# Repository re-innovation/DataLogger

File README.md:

# DataLogger
A remote datalogging system with many connectivity options.

Based upon the LinkIt One system on a chip board:

https://www.seeedstudio.com/LinkIt-ONE-p-2017.html

https://docs.labs.mediatek.com/resource/linkit-one/en/documentation

## Hardware

PCB has been designed in KiCAD and the files are available in this repository.

PCB has 2 x DC DC converters and a LiIon charger for recharging the battery.

3 x ACS1115 16 bit ADCs are used for monitoring the data.

## Software

The software has been written in C for upload via the Arduino IDE.

A configuration file is used on the SD card which lets the unit know how it needs to work. Set up can easily be done 'in the field'.

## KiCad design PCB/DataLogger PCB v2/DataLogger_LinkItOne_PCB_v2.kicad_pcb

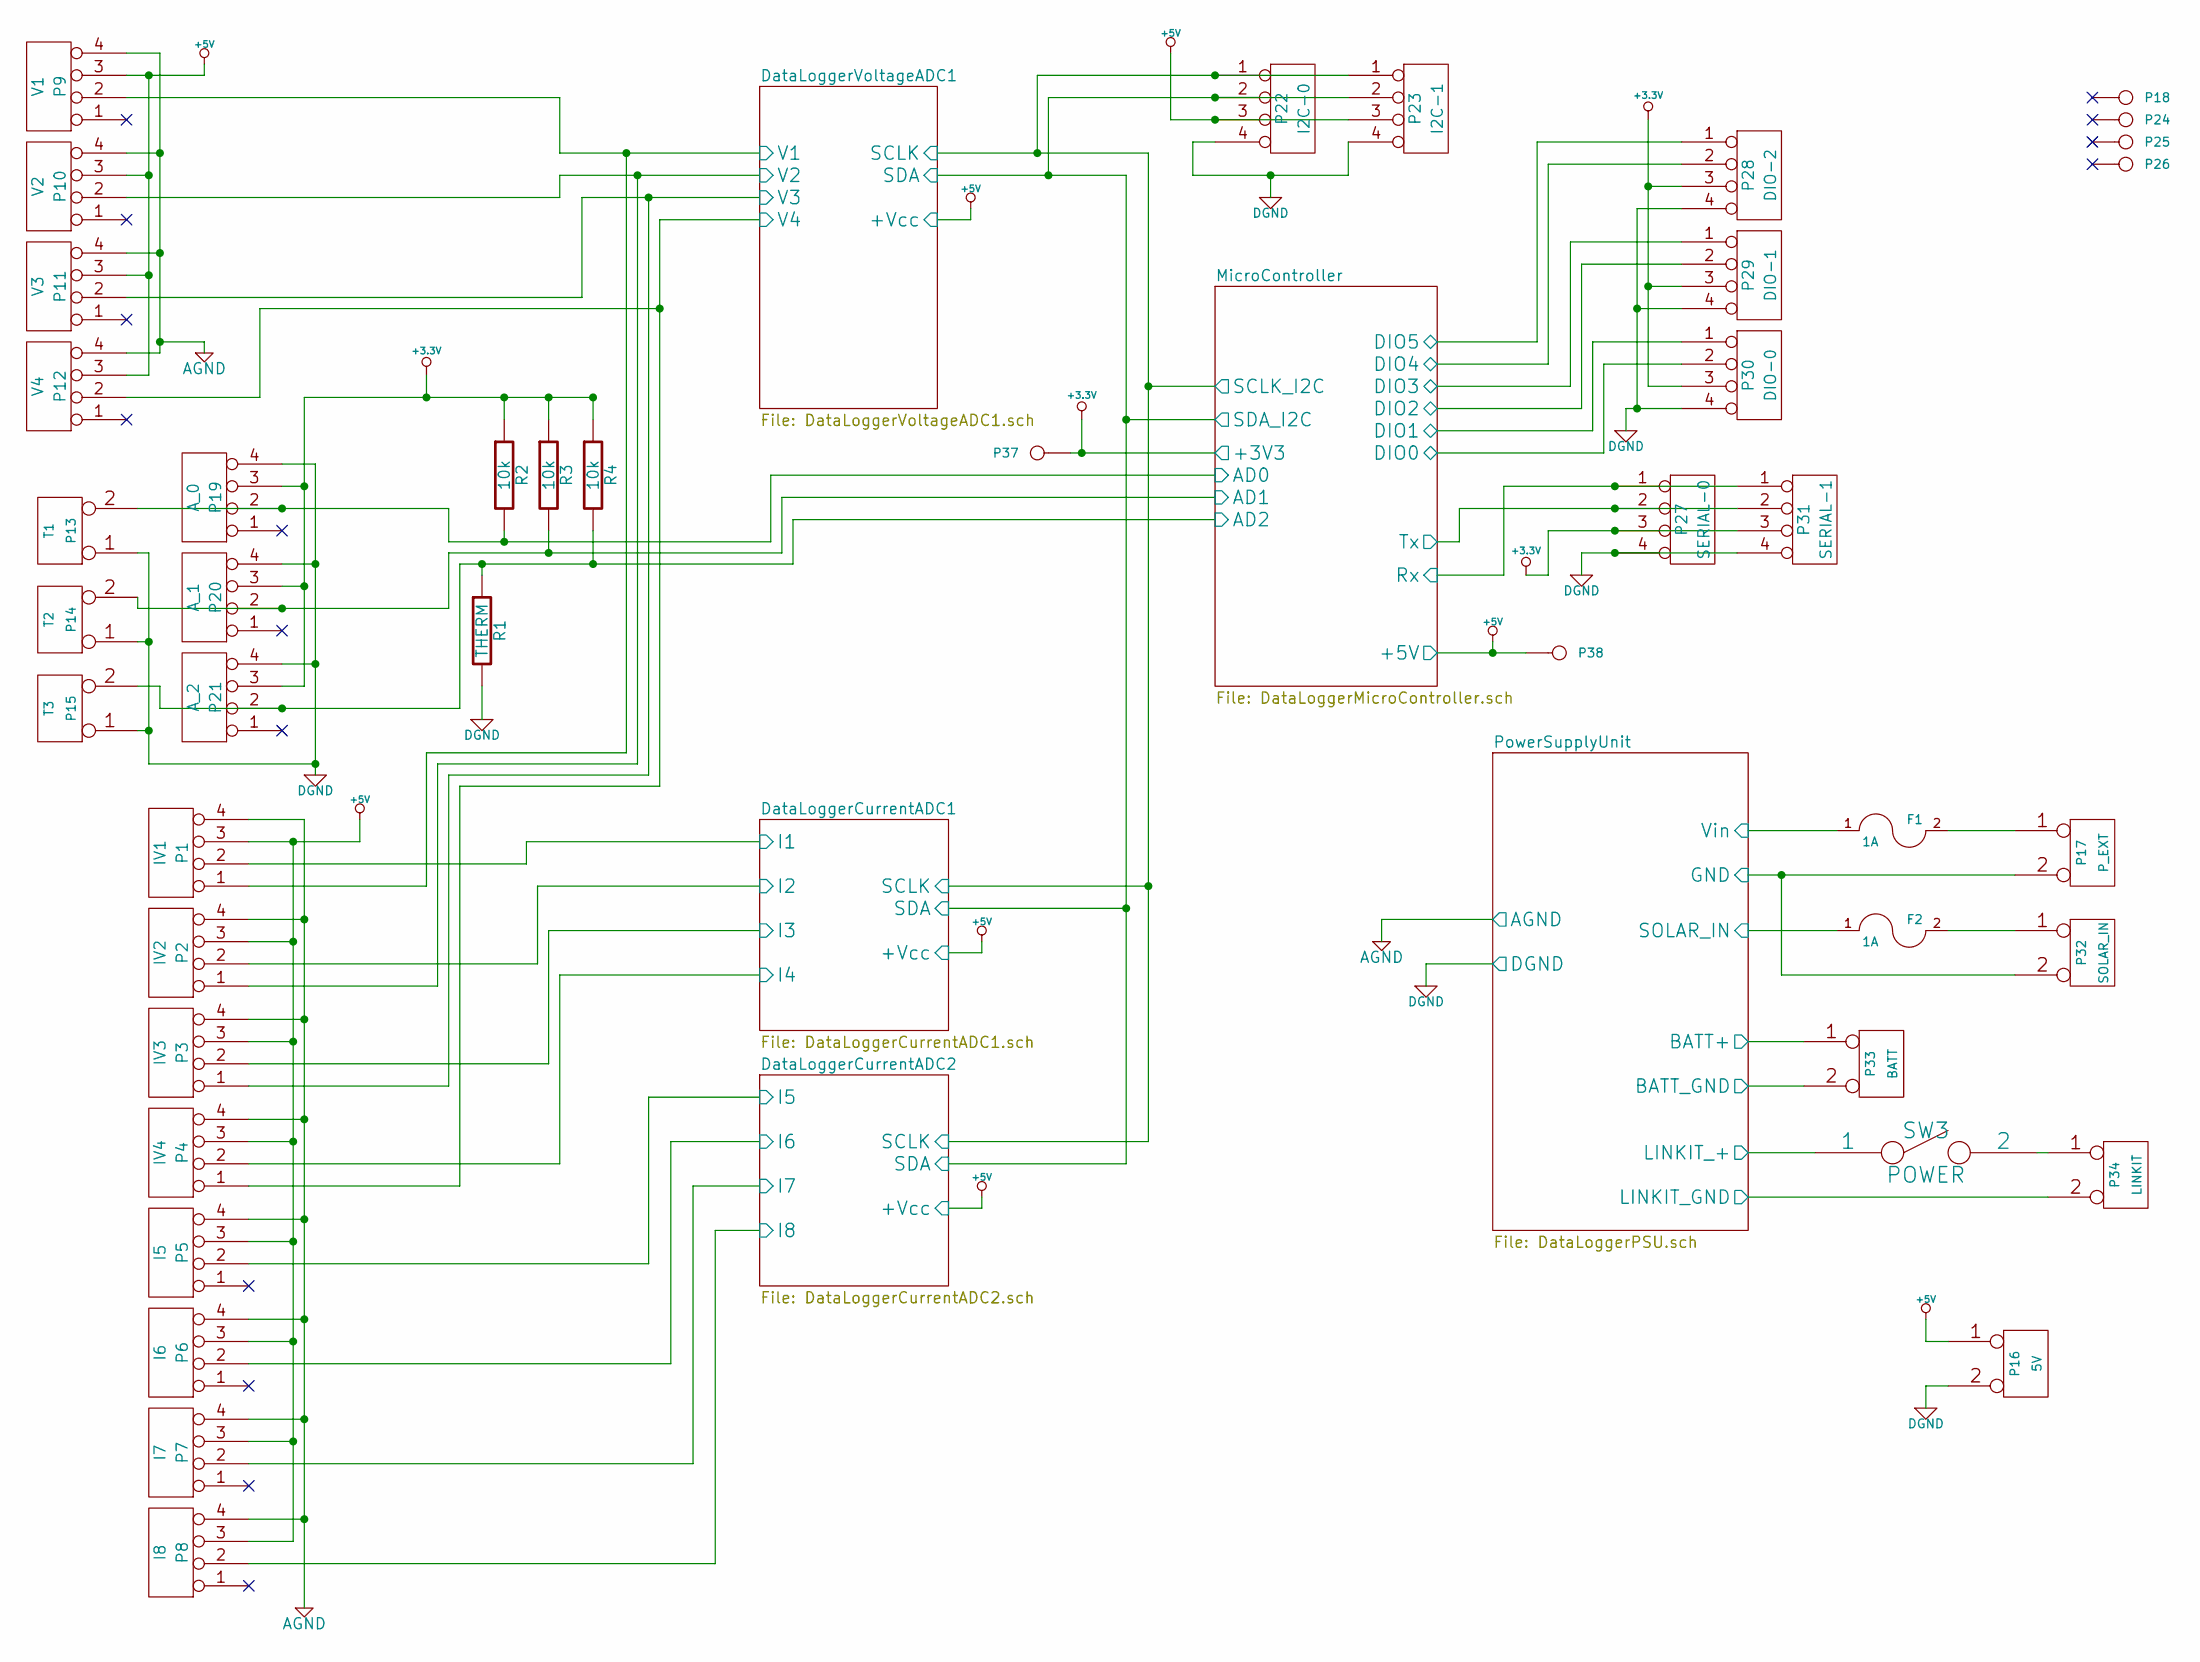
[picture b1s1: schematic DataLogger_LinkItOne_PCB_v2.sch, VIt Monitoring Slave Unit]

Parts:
F1, F2: 1A
P1: IV1
P2: IV2
P3: IV3
P4: IV4
P5: I5
P6: I6
P7: I7
P8: I8
P9: V1
P10: V2
P11: V3
P12: V4
P13: T1
P14: T2
P15: T3
P16: 5V
P17: P_EXT
P18, P24, P25, P26: CONN_1
P19: A_0
P20: A_1
P21: A_2
P22: I2C-0
P23: I2C-1
P27: SERIAL-0
P28: DIO-2
P29: DIO-1
P30: DIO-0
P31: SERIAL-1
P32: SOLAR_IN
P33: BATT
P34: LINKIT
P37: TP33V
P38: TP5V
R1: THERM
R2, R3, R4: 10k
SW3: POWER

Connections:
+3.3V: P19.3, P20.3, P21.3, P27.3, P28.3, P29.3, P30.3, P31.3, P37.1, R2.1, R3.1, R4.1; also elsewhere on the board
+5V: P1.3, P2.3, P3.3, P4.3, P5.3, P6.3, P7.3, P8.3, P9.3, P10.3, P11.3, P12.3, P16.1, P22.3, P23.3, P38.1; also elsewhere on the board
/DataLoggerCurrentADC1/I1: P1.2; also elsewhere on the board
/DataLoggerCurrentADC1/I2: P2.2; also elsewhere on the board
/DataLoggerCurrentADC1/I3: P3.2; also elsewhere on the board
/DataLoggerCurrentADC1/I4: P4.2; also elsewhere on the board
/DataLoggerCurrentADC1/SCLK: P22.1, P23.1; also elsewhere on the board
/DataLoggerCurrentADC1/SDA: P22.2, P23.2; also elsewhere on the board
/DataLoggerCurrentADC2/I5: P5.2; also elsewhere on the board
/DataLoggerCurrentADC2/I6: P6.2; also elsewhere on the board
/DataLoggerCurrentADC2/I7: P7.2; also elsewhere on the board
/DataLoggerCurrentADC2/I8: P8.2; also elsewhere on the board
/DataLoggerVoltageADC1/V1: P1.1, P9.2; also elsewhere on the board
/DataLoggerVoltageADC1/V2: P2.1, P10.2; also elsewhere on the board
/DataLoggerVoltageADC1/V3: P3.1, P11.2; also elsewhere on the board
/DataLoggerVoltageADC1/V4: P4.1, P12.2; also elsewhere on the board
/MicroController/AD0: P13.2 (PM), P19.2, R2.2; also elsewhere on the board
/MicroController/AD1: P14.2 (PM), P20.2, R3.2; also elsewhere on the board
/MicroController/AD2: P15.2 (PM), P21.2, R1.1, R4.2; also elsewhere on the board
/MicroController/DIO0: P30.2; also elsewhere on the board
/MicroController/DIO1: P30.1; also elsewhere on the board
/MicroController/DIO2: P29.2; also elsewhere on the board
/MicroController/DIO3: P29.1; also elsewhere on the board
/MicroController/DIO4: P28.2; also elsewhere on the board
/MicroController/DIO5: P28.1; also elsewhere on the board
/MicroController/Rx: P27.1, P31.1; also elsewhere on the board
/MicroController/Tx: P27.2, P31.2; also elsewhere on the board
/PowerSupplyUnit/BATT+: P33.1, SW3.1; also elsewhere on the board
/PowerSupplyUnit/SOLAR_IN: F2.1; also elsewhere on the board
/PowerSupplyUnit/Vin: F1.1; also elsewhere on the board
AGND: P1.4, P2.4, P3.4, P4.4, P5.4, P6.4, P7.4, P8.4, P9.4, P10.4, P11.4, P12.4; also elsewhere on the board
DGND: P13.1, P14.1, P15.1, P16.2 (PM), P17.2 (PM), P19.4, P20.4, P21.4, P22.4, P23.4, P27.4, P28.4, P29.4, P30.4, P31.4, P32.2 (PM), P33.2 (PM), P34.2 (PM), R1.2; also elsewhere on the board
unnamed: F1.2, P17.1
unnamed: P34.1, SW3.2
unnamed: F2.2, P32.1

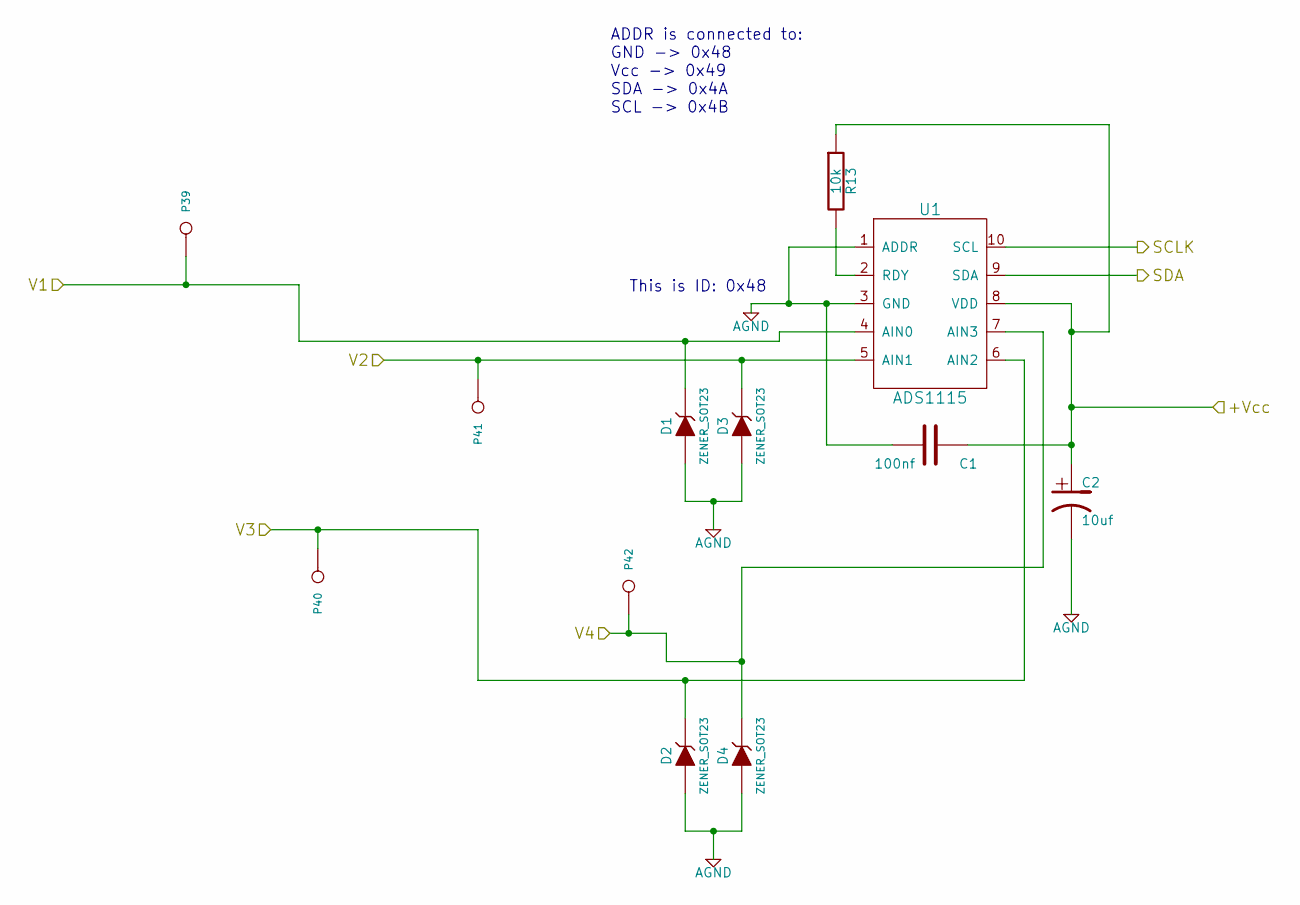
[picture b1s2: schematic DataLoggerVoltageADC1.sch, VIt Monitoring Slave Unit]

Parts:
C1: 100nf
C2: 10uf
D1, D2, D3, D4: ZENER_SOT23
P39: TPV1
P40: TPV3
P41: TPV2
P42: TPV4
R13: 10k
U1: ADS1115

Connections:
+5V: C1.1, C2.1, R13.1, U1.8 (VDD); also elsewhere on the board
/DataLoggerCurrentADC1/SCLK: U1.10 (SCL); also elsewhere on the board
/DataLoggerCurrentADC1/SDA: U1.9 (SDA); also elsewhere on the board
/DataLoggerVoltageADC1/V1: D1.3 (K), P39.1, U1.4 (AIN0); also elsewhere on the board
/DataLoggerVoltageADC1/V2: D3.3 (K), P41.1, U1.5 (AIN1); also elsewhere on the board
/DataLoggerVoltageADC1/V3: D2.3 (K), P40.1, U1.6 (AIN2); also elsewhere on the board
/DataLoggerVoltageADC1/V4: D4.3 (K), P42.1, U1.7 (AIN3); also elsewhere on the board
AGND: C1.2, C2.2, D1.1 (A), D2.1 (A), D3.1 (A), D4.1 (A), U1.1 (ADDR), U1.3 (GND); also elsewhere on the board
unnamed: R13.2, U1.2 (RDY)

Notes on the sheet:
ADDR is connected to: GND -> 0x48 Vcc -> 0x49 SDA -> 0x4A SCL -> 0x4B
This is ID: 0x48

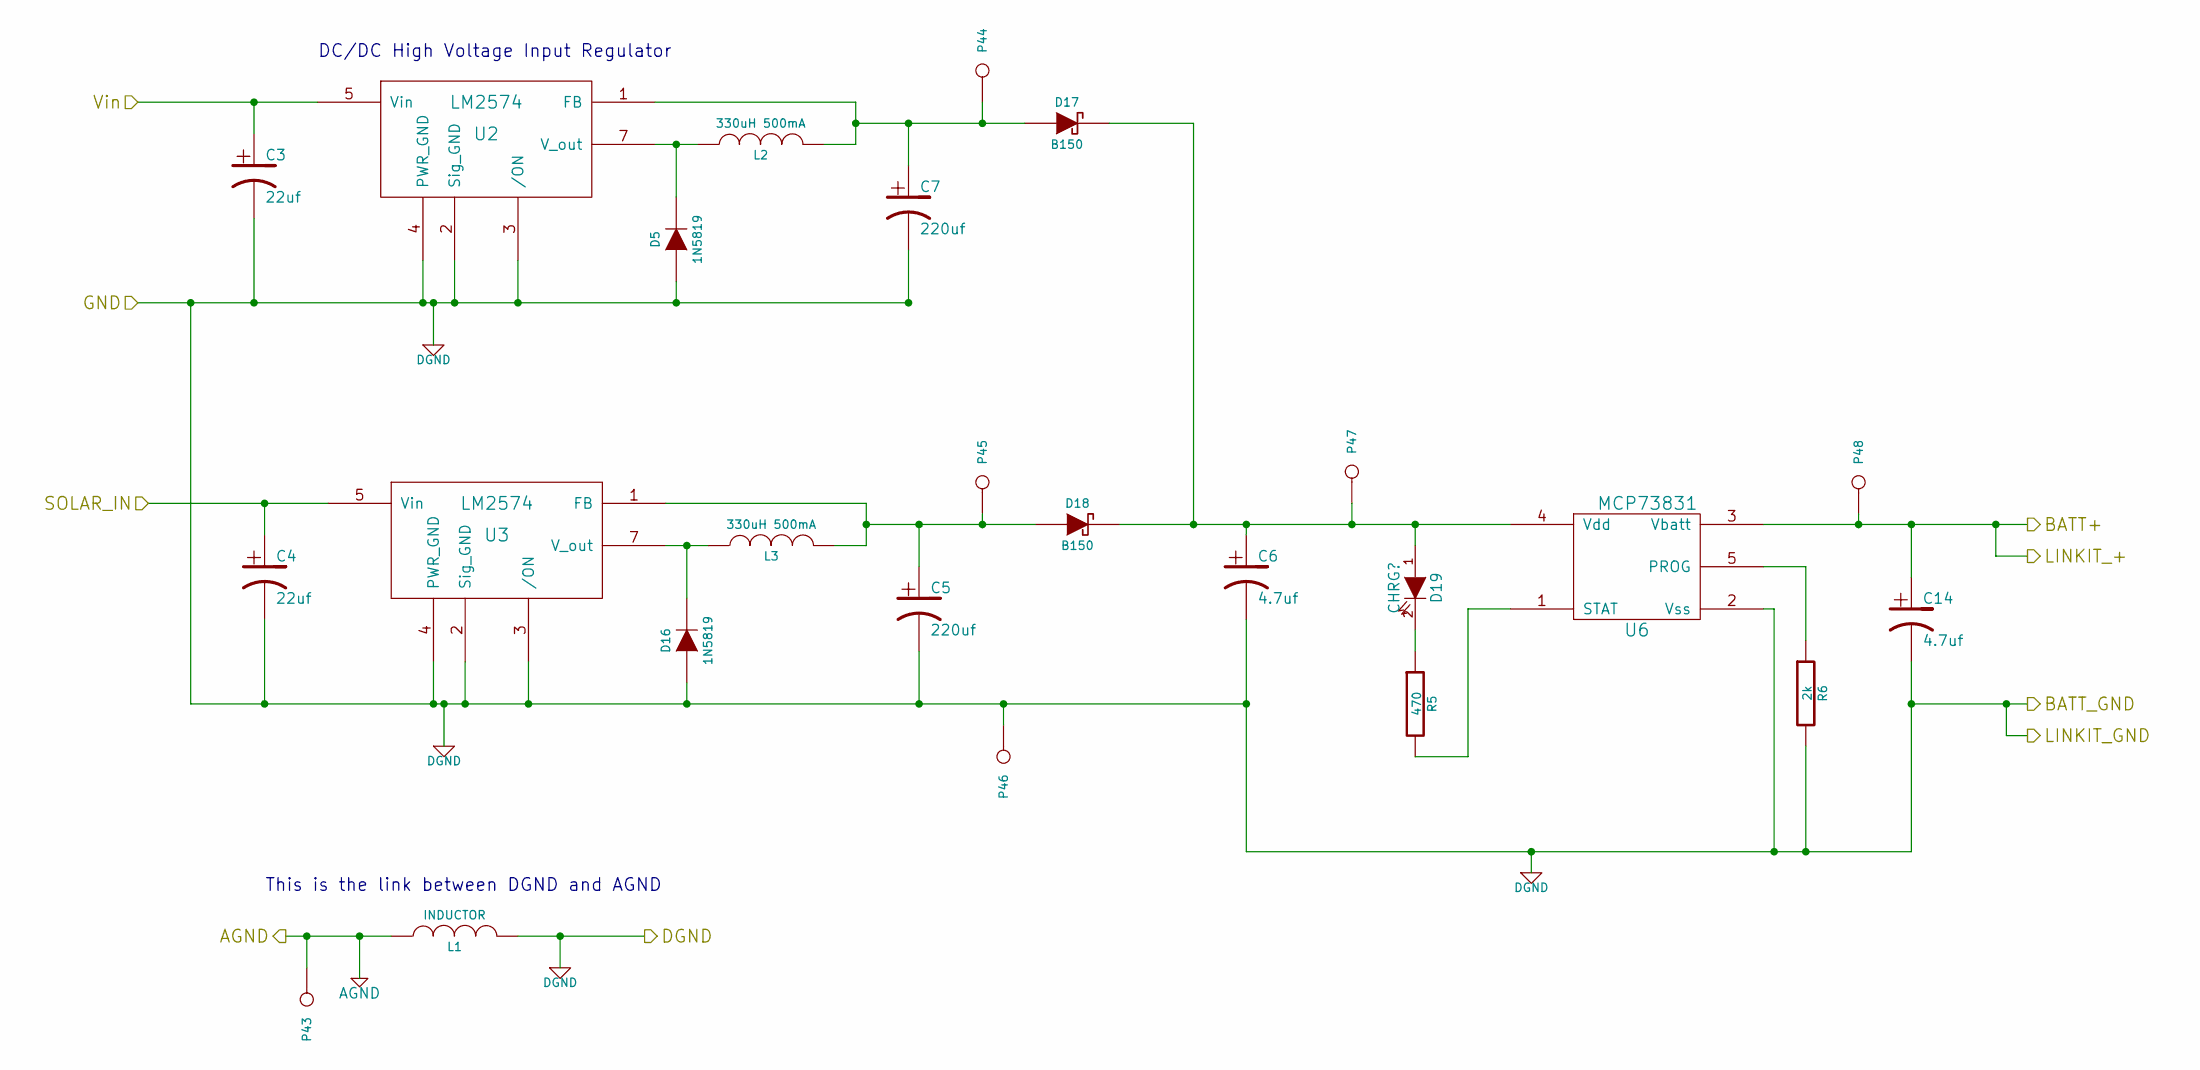
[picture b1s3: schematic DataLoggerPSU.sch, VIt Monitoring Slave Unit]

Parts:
C3, C4: 22uf
C5, C7: 220uf
C6, C14: 4.7uf
D5, D16: 1N5819
D17, D18: B150
D19: CHRG?
L1: INDUCTOR
L2, L3: 330uH 500mA
P43: TPAG
P44: TPP1
P45: TPP2
P46: TPDG
P47: TPP3
P48: TPBATT
R5: 470
R6: 2k
U2, U3: LM2574
U6: MCP73831

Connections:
/PowerSupplyUnit/BATT+: C14.1, P48.1, U6.3 (Vbatt); also elsewhere on the board
/PowerSupplyUnit/SOLAR_IN: C4.1, U3.5 (Vin); also elsewhere on the board
/PowerSupplyUnit/Vin: C3.1, U2.5 (Vin); also elsewhere on the board
AGND: L1.1, P43.1; also elsewhere on the board
DGND: C3.2, C4.2, C5.2, C6.2, C7.2, C14.2, D5.1 (A), D16.1 (A), L1.2, P46.1, R6.2, U2.2 (Sig_GND), U2.3 (/ON), U2.4 (PWR_GND), U3.2 (Sig_GND), U3.3 (/ON), U3.4 (PWR_GND), U6.2 (Vss); also elsewhere on the board
unnamed: R5.2, U6.1 (STAT)
unnamed: D19.2 (K), R5.1
unnamed: R6.1, U6.5 (PROG)
unnamed: D5.2 (K), L2.1, U2.7 (V_out)
unnamed: C7.1, D17.2 (A), L2.2, P44.1, U2.1 (FB)
unnamed: C6.1, D17.1 (K), D18.1 (K), D19.1 (A), P47.1, U6.4 (Vdd)
unnamed: C5.1, D18.2 (A), L3.2, P45.1, U3.1 (FB)
unnamed: D16.2 (K), L3.1, U3.7 (V_out)

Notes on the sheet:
DC/DC High Voltage Input Regulator
This is the link between DGND and AGND

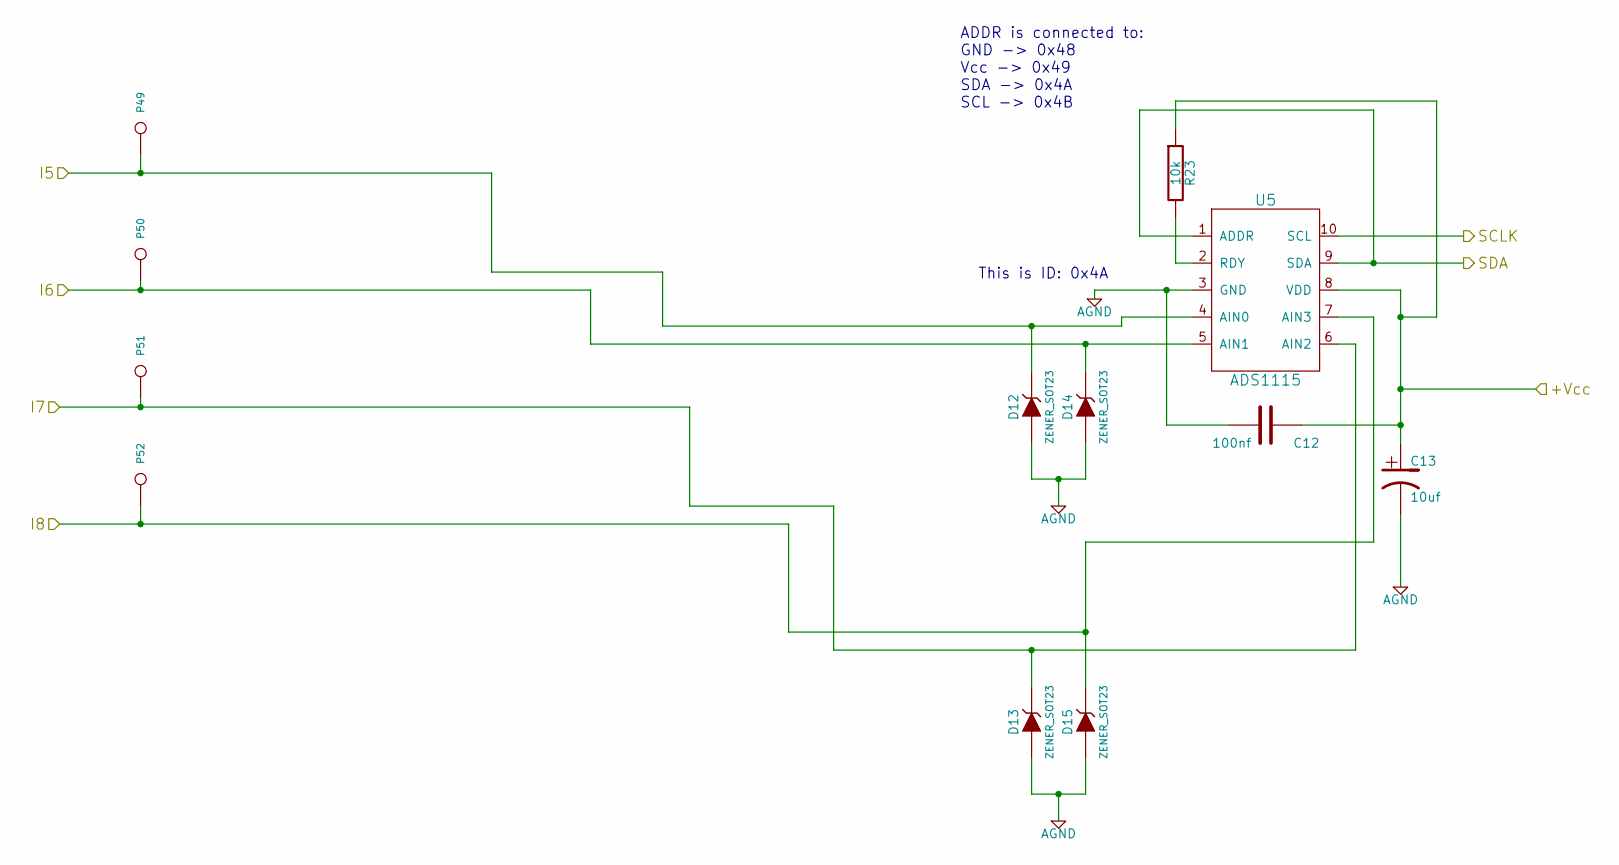
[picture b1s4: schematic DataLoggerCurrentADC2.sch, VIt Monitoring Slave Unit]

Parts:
C12: 100nf
C13: 10uf
D12, D13, D14, D15: ZENER_SOT23
P49: TPI5
P50: TPI6
P51: TPI7
P52: TPI8
R23: 10k
U5: ADS1115

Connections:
+5V: C12.1, C13.1, R23.1, U5.8 (VDD); also elsewhere on the board
/DataLoggerCurrentADC1/SCLK: U5.10 (SCL); also elsewhere on the board
/DataLoggerCurrentADC1/SDA: U5.1 (ADDR), U5.9 (SDA); also elsewhere on the board
/DataLoggerCurrentADC2/I5: D12.3 (K), P49.1, U5.4 (AIN0); also elsewhere on the board
/DataLoggerCurrentADC2/I6: D14.3 (K), P50.1, U5.5 (AIN1); also elsewhere on the board
/DataLoggerCurrentADC2/I7: D13.3 (K), P51.1, U5.6 (AIN2); also elsewhere on the board
/DataLoggerCurrentADC2/I8: D15.3 (K), P52.1, U5.7 (AIN3); also elsewhere on the board
AGND: C12.2, C13.2, D12.1 (A), D13.1 (A), D14.1 (A), D15.1 (A), U5.3 (GND); also elsewhere on the board
unnamed: R23.2, U5.2 (RDY)

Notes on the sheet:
ADDR is connected to: GND -> 0x48 Vcc -> 0x49 SDA -> 0x4A SCL -> 0x4B
This is ID: 0x4A

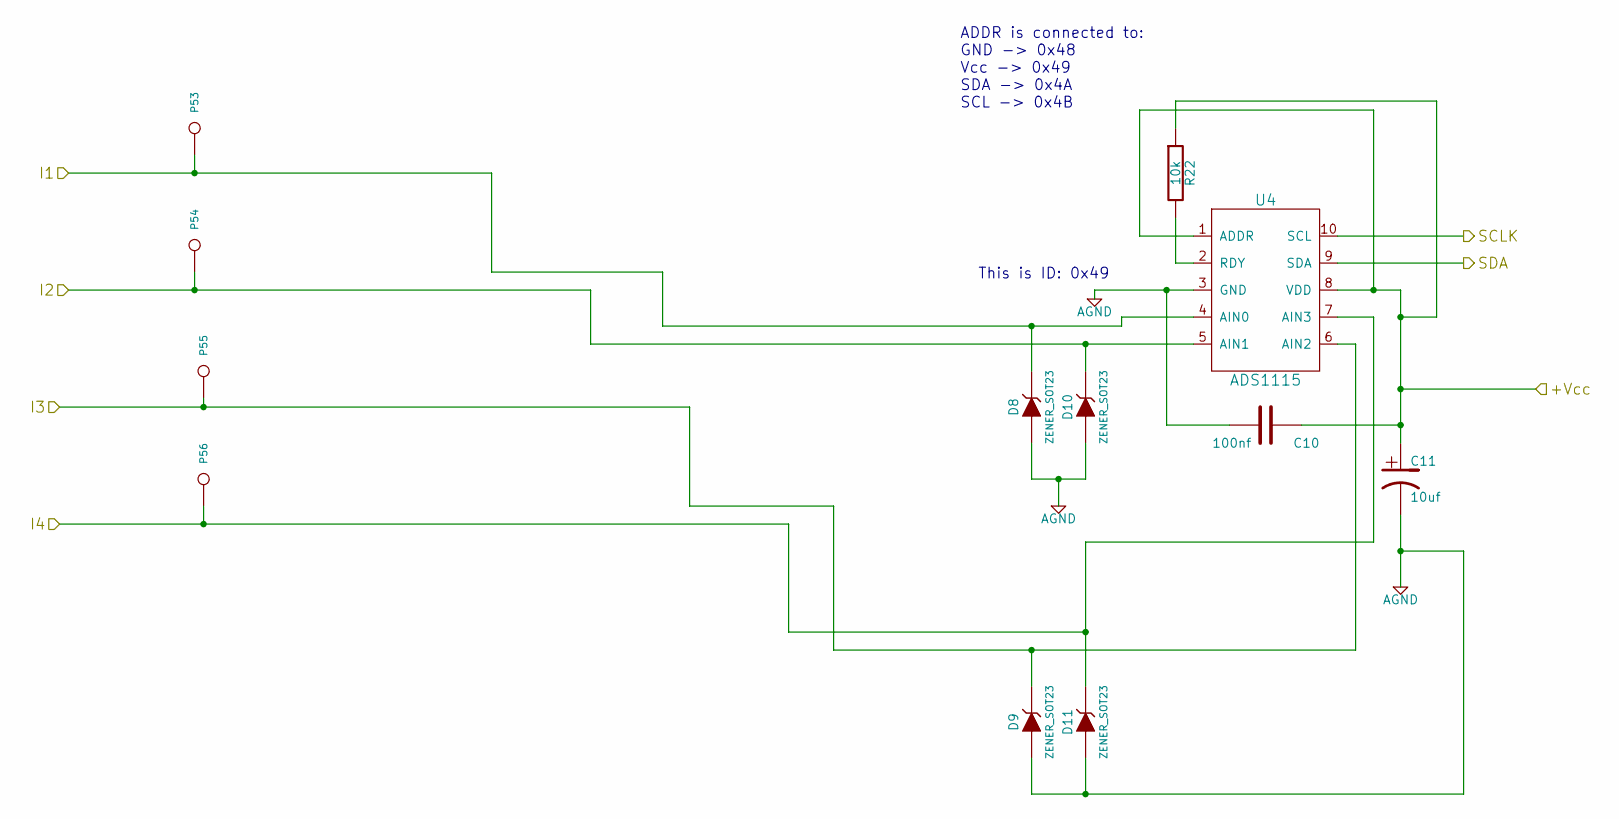
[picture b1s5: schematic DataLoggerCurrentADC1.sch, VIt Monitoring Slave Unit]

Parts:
C10: 100nf
C11: 10uf
D8, D9, D10, D11: ZENER_SOT23
P53: TPI1
P54: TPI2
P55: TPI3
P56: TPI4
R22: 10k
U4: ADS1115

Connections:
+5V: C10.1, C11.1, R22.1, U4.1 (ADDR), U4.8 (VDD); also elsewhere on the board
/DataLoggerCurrentADC1/I1: D8.3 (K), P53.1, U4.4 (AIN0); also elsewhere on the board
/DataLoggerCurrentADC1/I2: D10.3 (K), P54.1, U4.5 (AIN1); also elsewhere on the board
/DataLoggerCurrentADC1/I3: D9.3 (K), P55.1, U4.6 (AIN2); also elsewhere on the board
/DataLoggerCurrentADC1/I4: D11.3 (K), P56.1, U4.7 (AIN3); also elsewhere on the board
/DataLoggerCurrentADC1/SCLK: U4.10 (SCL); also elsewhere on the board
/DataLoggerCurrentADC1/SDA: U4.9 (SDA); also elsewhere on the board
AGND: C10.2, C11.2, D8.1 (A), D9.1 (A), D10.1 (A), D11.1 (A), U4.3 (GND); also elsewhere on the board
unnamed: R22.2, U4.2 (RDY)

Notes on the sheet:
ADDR is connected to: GND -> 0x48 Vcc -> 0x49 SDA -> 0x4A SCL -> 0x4B
This is ID: 0x49

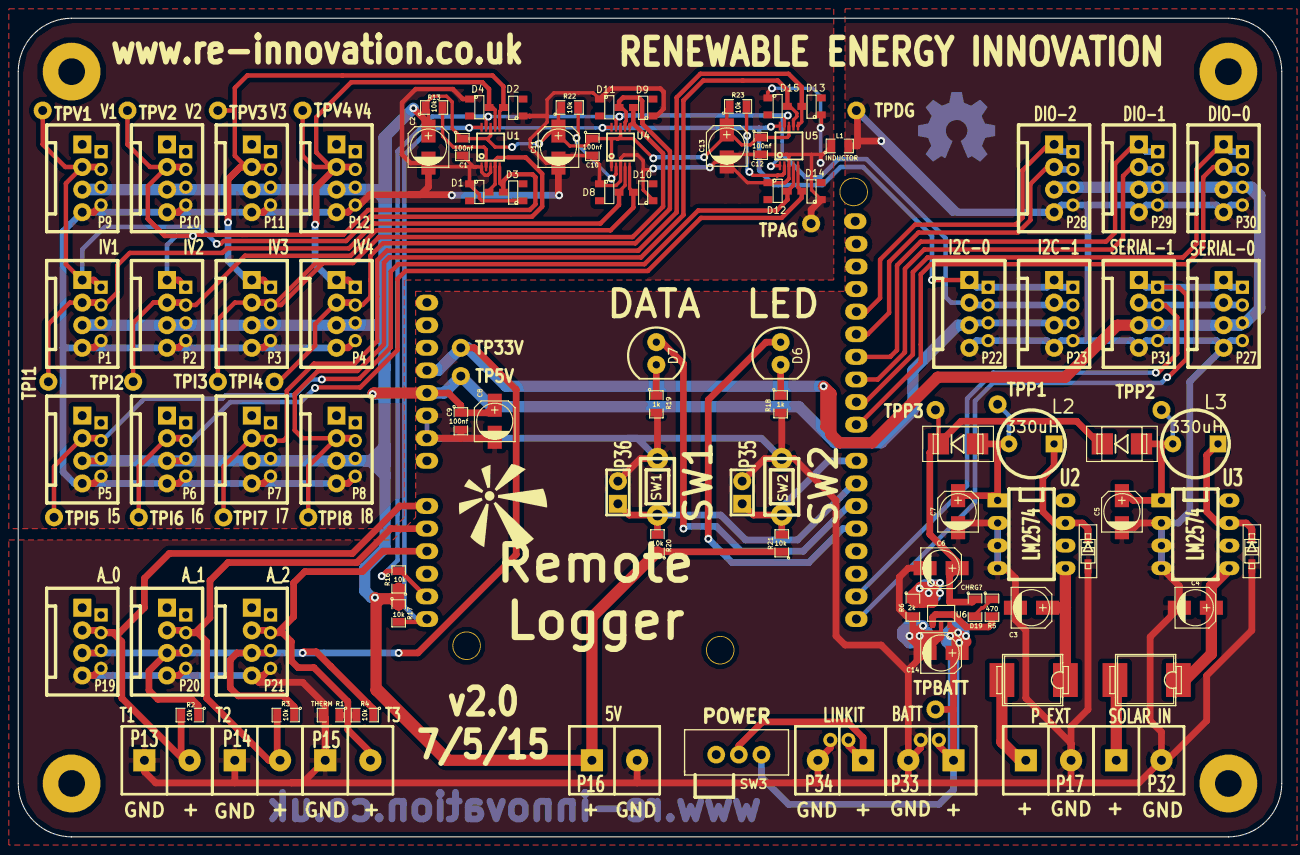
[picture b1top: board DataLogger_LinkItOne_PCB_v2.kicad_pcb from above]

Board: 2 copper layers, 142.0 x 92.0 mm, 121 parts (0 on the bottom side), 52 nets.

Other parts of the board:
C8: 10uf; c_elec_4x5.3
C9: 100nf; SM0805
D6: LED; LED-5MM_larg_pad
D7: DATA; LED-5MM_larg_pad
P35: SW2; SIL-2_lg_pad_1mm
P36: SW1; SIL-2_lg_pad_1mm
R16, R17, R20, R21: 10k; SM0805
R18, R19: 1k; SM0805
SHIELD1: LINKITONE_SHIELD; ARDUINO_SHIELD_LinkIt_ONE_no_edge
SW1: SW1; SW_PUSH_single_pins
SW2: SW2; SW_PUSH_single_pins
VAL: reinnovation_logo_15mm
VAL#2: OSHW_logo_small_back

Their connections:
+3.3V: SHIELD1.3V3; also elsewhere on the board
+5V: C8.1, C9.1, R16.1, R17.1, R20.1, R21.1, SHIELD1.5V; also elsewhere on the board
/DataLoggerCurrentADC1/SCLK: R17.2, SHIELD1.SCL; also elsewhere on the board
/DataLoggerCurrentADC1/SDA: R16.2, SHIELD1.SDA; also elsewhere on the board
/MicroController/AD0: SHIELD1.AD0; also elsewhere on the board
/MicroController/AD1: SHIELD1.AD1; also elsewhere on the board
/MicroController/AD2: SHIELD1.AD2; also elsewhere on the board
/MicroController/DIO0: SHIELD1.8; also elsewhere on the board
/MicroController/DIO1: SHIELD1.9; also elsewhere on the board
/MicroController/DIO2: SHIELD1.10; also elsewhere on the board
/MicroController/DIO3: SHIELD1.11; also elsewhere on the board
/MicroController/DIO4: SHIELD1.12; also elsewhere on the board
/MicroController/DIO5: SHIELD1.13; also elsewhere on the board
/MicroController/Rx: SHIELD1.0; also elsewhere on the board
/MicroController/Tx: SHIELD1.1; also elsewhere on the board
DGND: C8.2, C9.2, P35.2, P36.2, R18.2, R19.2, SHIELD1.GND1, SHIELD1.GND2, SW1.2, SW2.1; also elsewhere on the board
unnamed: D6.2, R18.1
unnamed: D7.2, R19.1
unnamed: D6.1, SHIELD1.4
unnamed: D7.1, SHIELD1.5
unnamed: P36.1, R20.2, SHIELD1.6, SW1.1
unnamed: P35.1, R21.2, SHIELD1.7, SW2.2

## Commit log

2015-02-13 Initial Commit of LinkIt ONE application and libraries
2015-02-15 Big re-arrangement of libraries
2015-02-15 Added tests and examples to libraries
2015-02-20 Added copy of TaskAction library
2015-02-20 Added readline utility header
2015-02-20 Refactoring of utility libraries
2015-02-20 Added mocks for i2c and delay
2015-02-20 Fixed comment
2015-02-20 Added ADS1x1x library and tests
    Based on Adafruit ADS1115 library
2015-02-20 Added .Test files to .gitignore
2015-02-20 Network interfaces can report connection state
2015-02-23 Added GPS utility library
2015-02-23 Incomplete Linkit ONE GPS library
2015-02-24 Added time module to utilities
2015-02-24 Update DLGPS library
2015-02-24 Unfinished support for HTTP post
2015-02-25 Added .exe files to gitignore
2015-02-25 Renamed "DLGPS" to "DLLocation"
2015-02-25 Added security library
2015-02-25 Added time library
2015-02-25 Added location utility library
2015-02-26 Fixed capitalisation of some functions
2015-02-27 Define guards around min/max macros
2015-02-27 Various fixes for arduino compatibility
2015-02-28 Additions to string utility library
2015-02-28 Continued dev on HTTP lib
2015-02-28 HTTP response parser handles reason line
2015-02-28 HTTP library handles simple request/reponse creation and, parsing
2015-03-02 HTTP example command line applications
2015-03-03 Think the HTTP builder/response parser works now.
2015-03-03 Unfinished changes for linkitone HTTP library support
2015-03-04 More HTTP work
2015-03-04 Fixed uninitialized counter in request builder
2015-03-04 Added .stackdump to .gitignore
2015-03-04 Deleted unused optionparser.h header
2015-03-04 Made request builder example a bit cleverer
2015-03-05 Thingspeak now uses POST not GET
2015-03-05 Removed STL usage from security module
2015-03-05 GPS library fixes based on testing with real hardware
2015-03-05 Linkit One checks GPS validity
2015-03-05 Application tests security feature
2015-03-06 Added writeLine method to FixedLengthAccumulator
2015-03-07 Fixes for HTTP library based on bulk upload tests
2015-03-07 Addition of CSV upload for thingspeak service
2015-03-07 Application uses POST instead of GET
2015-03-13 Move thingspeak command line example to own folder
2015-03-13 Added thingspeak bulk upload example
2015-03-13 Fixed ADS1x1x library and added example
2015-03-13 Fixed capitalisation of function names
2015-03-13 Fixed integer overflow with ADS1x1x single ended read
2015-03-13 Added new example application (Thingspeak & ADC)
2015-03-20 Added SMS library
2015-03-20 Fixed SMS issues
2015-03-20 Removed mobile number
2015-03-21 SMS and security examples
2015-03-22 Started work on settings reader
2015-03-23 Basic settings reader functionality complete
2015-03-23 Added command line example for config file reader
2015-03-24 Added untested LinkIt ONE settings reader example
2015-03-25 Moved GPS to own library
2015-03-25 Added verification script
2015-03-25 Renamed readline example
2015-03-25 GPS time functionality
2015-03-26 Fixed LinkItONE settings reader example
2015-03-26 Started local storage example
2015-03-31 Datafield stores arrays of data
2015-04-01 DataField storage uses circular buffer
2015-04-01 Removed mistakenly added test file
2015-04-01 Added field type string getter
2015-04-01 DataField handles indexes up to UINT32_MAX
2015-04-01 Fixed Arduino example applications
2015-04-01 Added length funtion to accumulator
2015-04-01 Added strncpy_safe function
2015-04-02 Added DataField array string output
2015-04-02 Fixed commenting
2015-04-02 Started adding averager
2015-04-02 Made averager a class
2015-04-02 In progress application
2015-04-02 In-progress time library
2015-04-02 Added filename library
2015-04-02 Started example RTC application
2015-04-03 Added time example (untested)
2015-04-03 Finished time example
2015-04-03 Fixed year handling for LinkItONE time
2015-04-03 Fixes for DataField library
2015-04-03 Logs to SD card without timestamps
2015-04-03 Added timestamp write to thingspeak
2015-04-03 Moved CSV functionality to own library
2015-04-03 Added conversion module to example application
2015-04-03 In progress example of RTC time set from GPS
2015-04-04 Added define guards around PI
2015-04-04 WIP Sensor library additions
2015-04-04 Added time from GPS example
2015-04-06 Thermistor library
2015-04-06 Completed thermistor example
2015-04-06 Added WIP Crest application
2015-04-06 Changed datafield to use uint32_t
2015-04-06 WIP Crest application
2015-04-06 Fixed CSV read/write bug
2015-04-06 Moved data handling and SD to seperate files
2015-04-07 Moved define to settings
2015-04-07 Added home_set member to security
2015-04-09 CREST Application 2015-04-07
2015-04-09 WIP local storage example
2015-04-10 Added mock for local storage
2015-04-14 Completed local storage example
2015-04-20 Fixed Settings test
2015-04-20 Settings now accepts spaces and comments. Also has better error handling
2015-04-21 Channel settings parser
2015-04-21 Started update of applications
2015-04-22 Fixed all example applications
2015-04-22 Fixed DataField tests
2015-04-22 Added basic datafield manager
2015-04-22 NumericDataField uses floats internally - much easier to work with
2015-04-22 Moved writeHeadersToBuffer to DataFieldManager class
2015-04-22 Changed ADCAndLocalStorage to use DFManager
2015-04-22 Started move of application to use DFManager
2015-04-23 Further work on CREST application
2015-04-23 Removed build files added by mistake
2015-04-23 Added lots of mocks for arduino apps
2015-04-23 Mock correctly exits from fatal error
2015-04-23 Fixed time mocking
2015-04-25 Lots of work on setup and error detection
2015-04-25 Many improvements/features
2015-04-25 Moved settings read from file to settings module
2015-04-26 Work on datachannel settings reader and manager
2015-04-27 Refactoring of settings and datafield modules
2015-04-28 CREST application work
2015-04-28 Changing DataField to be a proper ring buffer
2015-04-29 Further CREST application work
2015-04-29 Crest application for review
2015-04-29 Added example conf files
2015-04-29 Crest application
2015-04-29 Separated storage and upload averages
2015-04-29 Investigating conversion issue
2015-04-30 Fixed off-by-one issue with adding conversions to fields
2015-05-01 Added thermistor highside/lowside selection
2015-05-19 Moved conversion rountines to own module
2015-05-25 Moved upload buffer calculation to app data
2015-05-25 Application matches latest app data changes
2015-05-25 Increased conversion time for ADS111x ADCs
2015-05-28 Changed ADC read period to 200ms (from 100ms)
2015-05-28 Fixed LED pin allocations and pinMode settings
2015-05-28 Better information at startup
2015-05-28 Changed datafield count function to fieldCount
2015-05-30 WIP changes to Crest application
2015-06-01 Rewrite of datafield counting functionality
2015-06-01 Addition of basic debugging to taskaction
2015-06-01 Added serial output of time
2015-06-01 Added battery level SMS to application
2015-06-03 Separated general and maintenance numbers
2015-06-05 Completed battery SMS warning functionality
2015-06-05 Removed commented out functionality from app.data.cpp
2015-06-05 Added tests for DataField conversions
2015-06-05 Simplified test for highside thermistor setting
2015-06-10 Latest CREST application
2015-06-14 Added extra conversion to datafield
2015-06-15 Added linkitone specific data conversions
2015-06-15 New potential divider library
2015-06-15 Added missing includes
2015-06-27 Thermistor fix
2015-07-03 Added error LED blinks
2015-07-10 Added simple blink sketch
2015-07-14 WIP enhancements and refactoring
2015-07-14 Added tests for errors module
2015-07-15 Finished Crest error handling
2015-07-15 Moved SMS messaging from app to library
2015-07-24 Added SD card presence testing
2015-07-24 Added SD card not present error
2015-08-27 Fix for data manager issue (storing data in wrong fields)
2015-08-27 Corrected spelling
2015-08-27 Fixed failing sensor test
2015-10-02 Added offset and multiplier for voltage channels
2015-10-02 Removed un-needed comment from Crest application
2015-10-15 Added SD timestamp update
2015-10-15 Added unit identifier setting
2016-01-15 Added simple ADC example
2016-01-15 ADC and local storage bought up to date
2016-01-15 Added log folders to gitignore
2016-01-15 Removed other applications from Crest branch
2016-01-15 Removed all applications from master branch
2016-02-08 Added serial interface module and tests
2016-02-12 Added serial handling incomplete to application.
2016-02-14 Extra logging in application and network
2016-02-24 Completed serial interface work
2016-02-24 Added serial request test utility
2018-02-17 Added PCB design to the software
2018-02-17 Added documentaiotn and readme update
2018-04-26 Added .ino file
2020-08-17 Adding CREST logger files which work!
